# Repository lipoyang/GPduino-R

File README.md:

GPduino-R
=========

## 概要
GPduino-Rは、ESP8266搭載のWiFiロボット制御ボードです。

以下のことができます。
* ラジコンサーボ最大16個を制御
* DCモータ2個を制御 (最大連続1.2A / 最大瞬間3.0A)
* 電源 3.6V～7.2V (4.8～6V推奨)、電源電圧を監視
* WiFiによる通信　(APにもSTAにもなれる)

## ファイル一覧

* hard/GPduino-R/
	* GPduino-R.sch/brd: 回路/基板設計データ(Eagle形式)
	* GPduino-R.pdf: 回路図(PDF)
	* GPduino-R_BOM.xlsx: BOMリスト(Excel形式)
	* GPduino-R.GBL/GBO/GBP/GBS/GML/GTL/GTO/GTP/GTS/TXT: ガーバデータ
* firm/
	* GPduinoR/: Arduinoライブライリ
	* Mini4LD/Mini4LD.ino: 四足歩行ロボットのArduinoスケッチ
* LICENSE: Apache Licence 2.0です。
	* ただし、回路/基板設計は、Creative Commons Attribution Share-Alike 3.0です。
* README.md これ

## Arduino開発環境のセットアップ
GPduino-R はESP8266を搭載しており、Arduinoでファームウェアを開発できます。

* まず、ArduinoIDE をインストールしておきます。 (ここでは 1.6.9 を使用)
* [ファイル] > [環境設定] > [Additional Boards Manager URLs:]に下記URLをコピペ
	* http://arduino.esp8266.com/stable/package_esp8266com_index.json (安定版)
	* http://arduino.esp8266.com/staging/package_esp8266com_index.json (開発版)
* [ツール] > [ボード] > [ボードマネージャ] で [esp8266] をインストール
* [ツール] > [ボード] で [Generic ESP8266 Module]を選択
	* Flash Mode : QIO
	* Flash Frequency : 40MHz
	* Upload Using : Serial
	* CPU Frequency : 80MHz
	* Flash Size : 4M(3M SPIFFS)　(3MBをファイルシステムで使用 / 1MBをスケッチで使用)
	* Debug port : Disabled
	* Debug Level : None
	* Reset Method : nodemcu
	* Upload Speed : 115200

## Arduinoライブラリのインストール

firm/ にある GPduinoR/ フォルダを、Arduinoのライブラリフォルダにコピーします。

Arduinoのライブラリフォルダは、以下の場所です。
* Documents/Arduino/libraries (Windows10, Mac, Linux)
* My Documents/Arduino/libraries (Windows7)

## Arduinoスケッチの作成
GPduinoR.h をインクルードします。
``` c
#include <GPduinoR.h>
```
すると、以下のオブジェクトが使用できます。詳細は、GPduinoR/フォルダにあるソースを参照してください。
- Battery: バッテリー電圧の取得
- DcMotor: DCモータの制御
- RcServo: ラジコンサーボの制御
- UdpComm: WiFiによるUDP/IP通信

Mini4LD/Mini4LD.ino は、四足歩行ロボット([歩くミニ四駆](https://www.youtube.com/watch?v=Bx3RYRKqrKQ))のArduinoスケッチです。参考にしてください。

## Arduinoスケッチの書き込み

* GPduino-RをUSBケーブルでPCに接続します。
* 書き込み時もUSBからの給電は受けません。CN1から給電してください。
* Windows 7以降であればドライバが自動でインストールされ、COMポートとして認識されます。
	* 自動でデバイスが認識されない環境ではFTDIのデバイスドライバをインストールしてください。
* [ツール] > [シリアルポート]でGPduino-RのCOMポート番号を指定します。
* BOOTボタン(SW2)を押し下げた状態で、RESETボタン(SW1)を押して離します。
* Uploadボタンで、ファームウェアを書き込みます。

## 既知の問題点
* サーボのコネクタの間隔が狭すぎる。(干渉して16個全部を接続できない)

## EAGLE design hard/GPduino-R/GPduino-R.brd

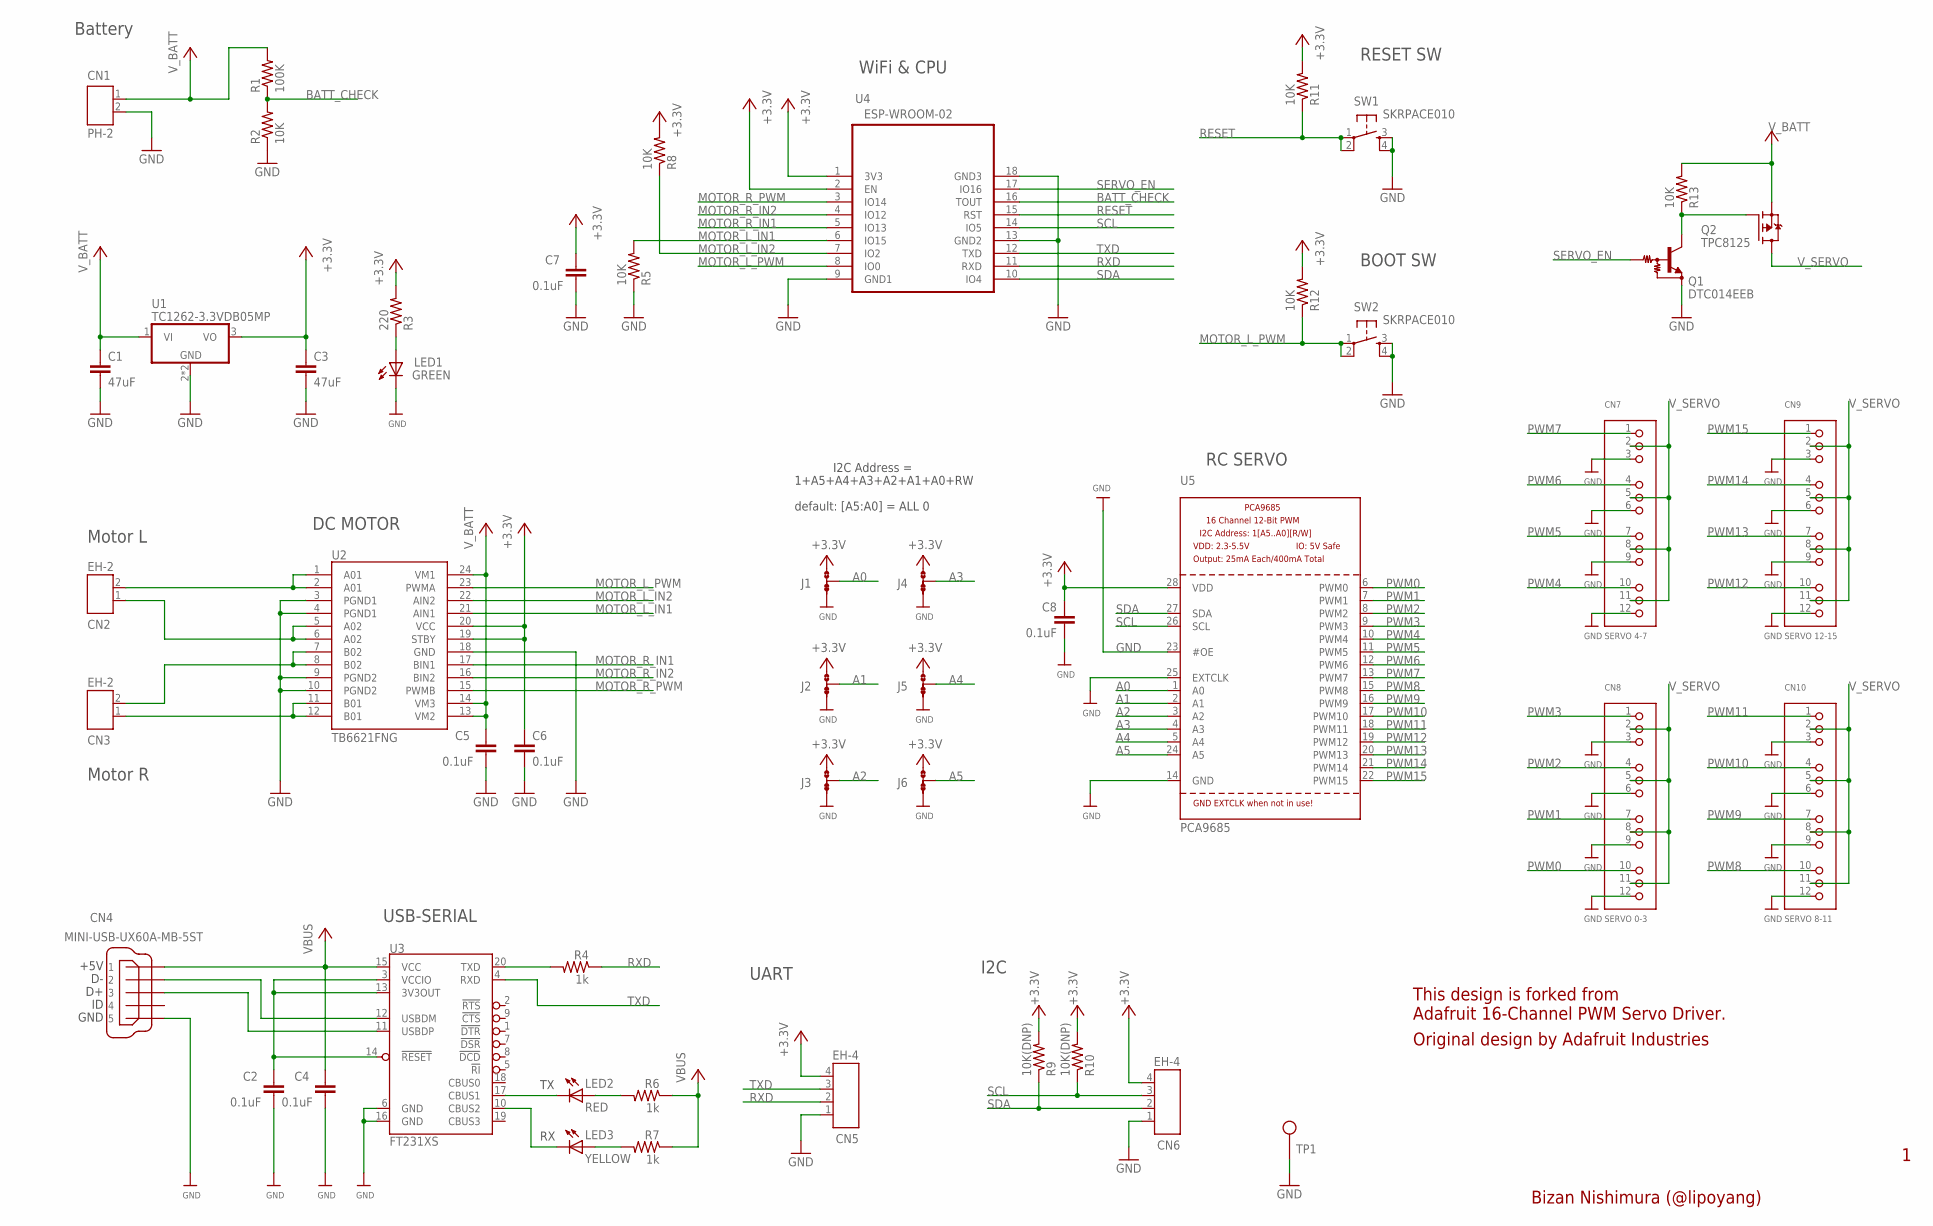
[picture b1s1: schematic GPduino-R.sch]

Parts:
C1, C3: 47uF; C3216
C2, C4, C5, C6, C7, C8: 0.1uF; C1608
CN1: PH-2
CN2, CN3: EH-2
CN4: MINI-USB-UX60A-MB-5ST; UX60A-MB-5ST
CN5, CN6: EH-4
CN7: SERVO 4-7; 3X04
CN8: SERVO 0-3; 3X04
CN9: SERVO 12-15; 3X04
CN10: SERVO 8-11; 3X04
J1, J2, J3, J4, J5, J6: JUMP-SHORTB; JUMP-SHORT
LED1: GREEN; CHIPLED_0603
LED2: RED; CHIPLED_0603
LED3: YELLOW; CHIPLED_0603
Q1: DTC014EEB; SOT490
Q2: TPC8125; SO-8
R1: 100K; 0603-RES
R2, R5, R8, R11, R12, R13: 10K; 0603-RES
R3: 220; 0603-RES
R4, R6, R7: 1k; 0603-RES
R9, R10: 10K(DNP); 0603-RES
SW1, SW2: SKRPACE010
TP1: TEST_PIN
U1: TC1262-3.3VDB05MP; SOT223
U2: TB6621FNG; SSOP24
U3: FT231XS; SSOP20
U4: ESP-WROOM-02; FRONT-FACE
U5: PCA9685; TSSOP28

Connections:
+3V3: C3.1, C6.1, C7.1, C8.1, CN5.4, CN6.4, J1.1, J2.1, J3.1, J4.1, J5.1, J6.1, R3.2, R8.2, R9.2, R10.2, R11.2, R12.2, U1.3 (VO), U2.19 (STBY), U2.20 (VCC), U4.1 (3V3), U4.2 (EN), U5.28 (VDD)
A0: J1.2, U5.1 (A0)
A01: CN2.2, U2.1 (A01), U2.2 (A01)
A1: J2.2, U5.2 (A1)
A02: CN2.1, U2.5 (A02), U2.6 (A02)
A2: J3.2, U5.3 (A2)
A3: J4.2, U5.4 (A3)
A4: J5.2, U5.5 (A4)
A5: J6.2, U5.24 (A5)
BATT_CHECK: R1.1, R2.2, U4.16 (TOUT)
GND: C1.2, C2.2, C3.2, C4.2, C5.2, C6.2, C7.2, C8.2, CN1.2, CN4.5, CN5.1, CN6.1, CN7.3, CN7.6, CN7.9, CN7.12, CN8.3, CN8.6, CN8.9, CN8.12, CN9.3, CN9.6, CN9.9, CN9.12, CN10.3, CN10.6, CN10.9, CN10.12, J1.3, J2.3, J3.3, J4.3, J5.3, J6.3, LED1.C, Q1.2 (E), R2.1, R5.1, SW1.3, SW1.4, SW2.3, SW2.4, TP1.1, U1.2 (GND), U1.4 (GND), U2.3 (PGND1), U2.4 (PGND1), U2.9 (PGND2), U2.10 (PGND2), U2.18 (GND), U3.6 (GND), U3.16 (GND), U4.9 (GND1), U4.13 (GND2), U4.18 (GND3), U5.14 (GND), U5.23 (#OE), U5.25 (EXTCLK)
MOTOR_L_IN1: R5.2, U2.21 (AIN1), U4.6 (IO15)
MOTOR_L_IN2: R8.1, U2.22 (AIN2), U4.7 (IO2)
MOTOR_L_PWM: R12.1, SW2.1, SW2.2, U2.23 (PWMA), U4.8 (IO0)
MOTOR_R_IN1: U2.17 (BIN1), U4.5 (IO13)
MOTOR_R_IN2: U2.16 (BIN2), U4.4 (IO12)
MOTOR_R_PWM: U2.15 (PWMB), U4.3 (IO14)
unnamed: LED1.A, R3.1
unnamed: R4.2, U3.20 (TXD)
unnamed: CN3.1, U2.11 (B01), U2.12 (B01)
unnamed: CN3.2, U2.7 (B02), U2.8 (B02)
unnamed: LED2.C, U3.17 (CBUS1)
unnamed: LED3.C, U3.10 (CBUS2)
unnamed: LED2.A, R6.2
unnamed: LED3.A, R7.2
unnamed: CN4.2, U3.12 (USBDM)
unnamed: CN4.3, U3.11 (USBDP)
unnamed: C2.1, U3.3 (VCCIO), U3.13 (3V3OUT), U3.14 (!RESET)
unnamed: Q1.3 (C), Q2.4 (G), R13.1
PWM0: CN8.10, U5.6 (PWM0)
PWM1: CN8.7, U5.7 (PWM1)
PWM2: CN8.4, U5.8 (PWM2)
PWM3: CN8.1, U5.9 (PWM3)
PWM4: CN7.10, U5.10 (PWM4)
PWM5: CN7.7, U5.11 (PWM5)
PWM6: CN7.4, U5.12 (PWM6)
PWM7: CN7.1, U5.13 (PWM7)
PWM8: CN10.10, U5.15 (PWM8)
PWM9: CN10.7, U5.16 (PWM9)
PWM10: CN10.4, U5.17 (PWM10)
PWM11: CN10.1, U5.18 (PWM11)
PWM12: CN9.10, U5.19 (PWM12)
PWM13: CN9.7, U5.20 (PWM13)
PWM14: CN9.4, U5.21 (PWM14)
PWM15: CN9.1, U5.22 (PWM15)
RESET: R11.1, SW1.1, SW1.2, U4.15 (RST)
RXD: CN5.2, R4.1, U4.11 (RXD)
SCL: CN6.3, R10.1, U4.14 (IO5), U5.26 (SCL)
SDA: CN6.2, R9.1, U4.10 (IO4), U5.27 (SDA)
SERVO_EN: Q1.1 (B), U4.17 (IO16)
TXD: CN5.3, U3.4 (RXD), U4.12 (TXD)
VBUS: C4.1, CN4.1, R6.1, R7.1, U3.15 (VCC)
V_BATT: C1.1, C5.1, CN1.1, Q2.1 (S), Q2.2 (S), Q2.3 (S), R1.2, R13.2, U1.1 (VI), U2.13 (VM2), U2.14 (VM3), U2.24 (VM1)
V_SERVO: CN7.2, CN7.5, CN7.8, CN7.11, CN8.2, CN8.5, CN8.8, CN8.11, CN9.2, CN9.5, CN9.8, CN9.11, CN10.2, CN10.5, CN10.8, CN10.11, Q2.5 (D), Q2.6 (D), Q2.7 (D), Q2.8 (D)

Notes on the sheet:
Battery
Motor L
Bizan Nishimura (@lipoyang)
Motor R
I2C
1+A5+A4+A3+A2+A1+A0+RW
I2C Address =
default: [A5:A0] = ALL 0
UART
USB-SERIAL
DC MOTOR
RC SERVO
WiFi & CPU
RESET SW
BOOT SW
This design is forked from Adafruit 16-Channel PWM Servo Driver.
Original design by Adafruit Industries

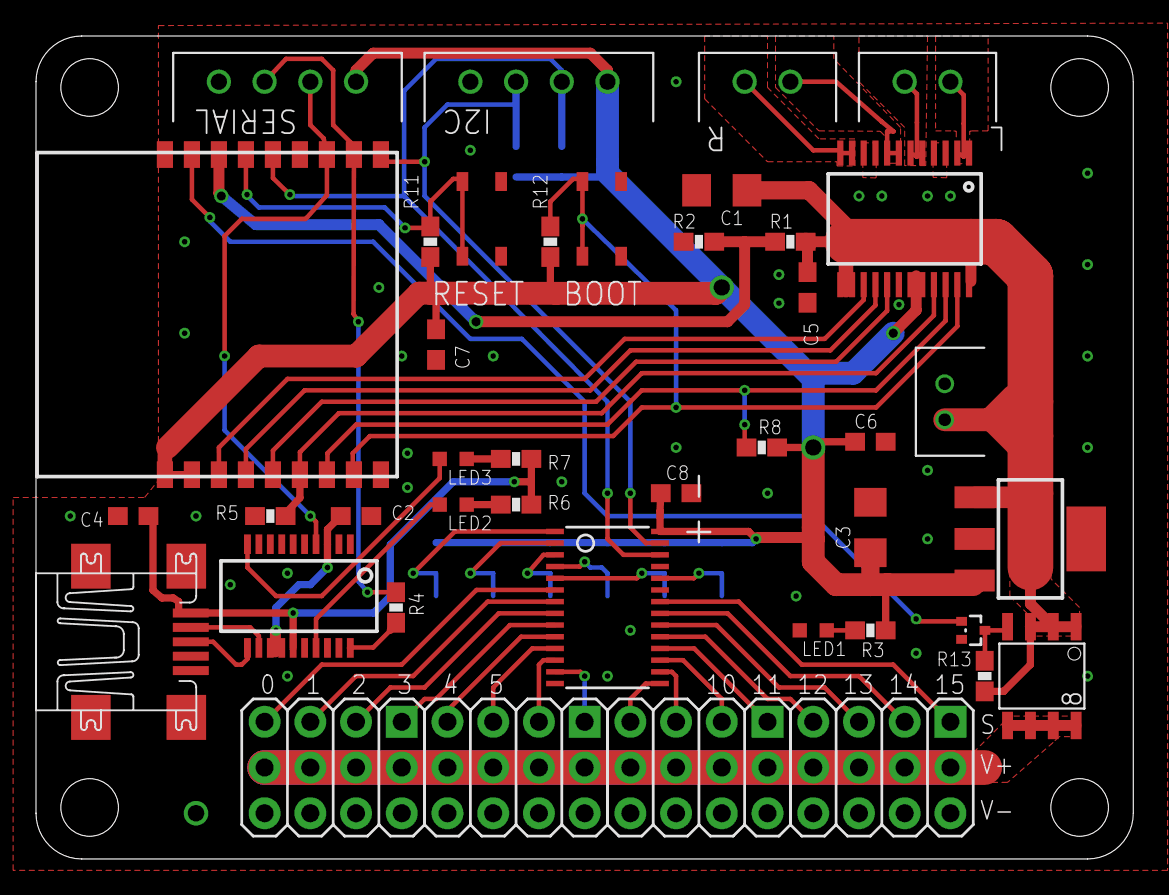
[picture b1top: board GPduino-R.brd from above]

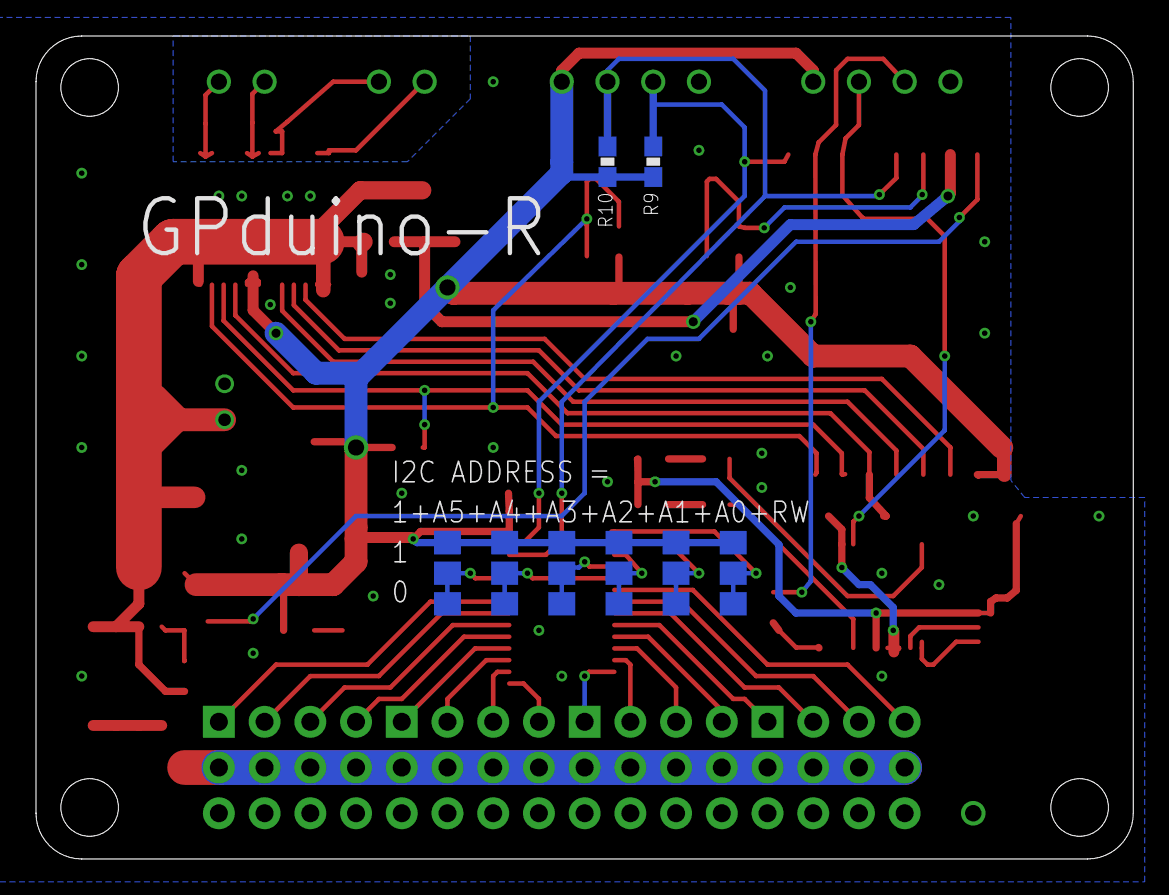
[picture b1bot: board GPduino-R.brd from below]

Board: 2 copper layers, 61.0 x 45.7 mm, 50 parts (8 on the bottom side), 54 nets.

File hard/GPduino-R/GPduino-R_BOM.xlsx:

No | Reference | Part Number | Vender | Description | DNP | Qty | Unit Price | Price | Lot Size | Supplier | Supplier Code
1 | C1,3 | 47u(3216) | (generic) | 3216型ガタ |  | 2 | 30 | 60 | 10 | 秋月アキヅキ | P-06040
2 | C2,4,5,6,7,8 | 0.1u(1608) | (generic) | 1608型ガタ |  | 6 | 0.32500000000000001 | 1.9500000000000002 | 4000 | 秋月アキヅキ | P-01299
3 | CN1 | S2B-PH-K-S | JST | PH 2極 L型ポストキョクガタ |  | 1 | 16 | 16 | 1 | 共立キョウリツ | -
4 | CN2,3 | B2B-EH-A | JST | EH 2極 I型ポストキョクガタ | DNP | 0 | 16 | 0 | 1 | 共立キョウリツ | -
5 | CN4 | MINI-USB-UX60A-MB-5ST | HRS | USB ミニB |  | 1 | 50 | 50 | 4 | 秋月アキヅキ | C-05690
6 | CN5,6 | B4B-EH-A | JST | EH 4極 I型ポストキョクガタ | DNP | 0 | 21 | 0 | 1 | 共立キョウリツ | -
7 | CN7,8,9,10 | - | (generic) | ピンヘッダ 3ピン×4 | DNP | 0 | 60 | 0 | 2 | 共立キョウリツ | -
8 | LED1 | OSYG1608 | OptoSupply | 1608型 GREENガタ |  | 1 | 10 | 10 | 20 | 秋月アキヅキ | I-03980
9 | LED2 | OSHR1608 | OptoSupply | 1608型 REDガタ |  | 1 | 10 | 10 | 20 | 秋月アキヅキ | I-03978
10 | LED3 | OSYL1608 | OptoSupply | 1608型 YELLOWガタ |  | 1 | 10 | 10 | 20 | 秋月アキヅキ | I-03984
11 | Q1 | DTC014EEB | ROHM | NPNデジタルトランジスタ |  | 1 | 3.2 | 3.2 | 200 | RS | 124-6536
12 | Q2 | TPC8125 | Toshiba | PMOS FET |  | 1 | 36.799999999999997 | 36.799999999999997 | 5 | RS | 756-3817
13 | R1 | 100k(1608) | (generic) | 1608型 |  | 1 | 0.2 | 0.2 | 2500 | 秋月アキヅキ | R-06104
14 | R2,5,8,11,12,13 | 10k(1608) | (generic) | 1608型 |  | 6 | 0.2 | 1.2000000000000002 | 2500 | 秋月アキヅキ | R-06103
15 | R3 | 220(1608) | (generic) | 1608型 |  | 1 | 0.2 | 0.2 | 2500 | 秋月アキヅキ | R-06221
16 | R4,R6,R7 | 1k(1608) | (generic) | 1608型 |  | 3 | 0.2 | 0.60000000000000009 | 2500 | 秋月アキヅキ | R-06102
17 | R9,R10 | 10k(1608) | (generic) | 1608型 | DNP | 0 | 0.2 | 0 | 2500 | 秋月アキヅキ | R-06103
18 | SW1,2 | SKRPACE010 | ALPS | 表面実装タクトスイッチヒョウメンジッソウ |  | 2 | 20 | 40 | 5 | 秋月アキヅキ | P-06185
20 | U1 | TC1262-3.3VDB05MP | Microchip | LDO, 3.3V-0.5A, SOT-223型ガタ |  | 1 | 81 | 81 | 1 | RS | 703-7905
21 | U2 | TB6621FNG | Toshiba | Dual DCモータドライバ |  | 1 | 306 | 306 | 1 | RS | 770-3797
22 | U3 | FT231XS | FTDI | USBシリアル変換ヘンカン |  | 1 | 210 | 210 | 1 | 秋月アキヅキ | I-06713
23 | U4 | ESP-WROOM-02 | Espressif Systems | ESP8266 WiFiモジュール |  | 1 | 550 | 550 | 1 | 秋月アキヅキ | M-09607
24 | U5 | PCA9685PW | NXP | PWMドライバ |  | 1 | 262 | 262 | 2 | RS | 727-5649
25 | - | - | Elecrow | 基板キバン |  | 1 | 260.10000000000002 | 260.10000000000002 | 10 | Elecrow | -
26 | - | PH2P300L | Marutsu | PH 2極 アッセンブルケーブルキョク |  | 1 | 54 | 54 | 1 | マルツ | -
 |  |  |  |  |  |  | Total | 1963.25

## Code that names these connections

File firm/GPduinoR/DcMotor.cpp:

#include <Arduino.h>

#define _DC_MOTOR_C_
#include <DcMotor.h>

// Pin Number
#define MOTOR_R_PWM    14
#define MOTOR_R_IN2    12
#define MOTOR_R_IN1    13
#define MOTOR_L_PWM    0
#define MOTOR_L_IN2    2
#define MOTOR_L_IN1    15

// begin the DC motor driver
void DcMotor_t::begin()
{
    // initialize PWM
    analogWrite(MOTOR_L_PWM, 0);
    analogWrite(MOTOR_R_PWM, 0);
    
    // initialize GPIO
    digitalWrite(MOTOR_L_IN1, LOW);
    digitalWrite(MOTOR_L_IN2, LOW);
    digitalWrite(MOTOR_R_IN1, LOW);
    digitalWrite(MOTOR_R_IN2, LOW);
    pinMode(MOTOR_L_IN1, OUTPUT);
    pinMode(MOTOR_L_IN2, OUTPUT);
    pinMode(MOTOR_R_IN1, OUTPUT);
    pinMode(MOTOR_R_IN2, OUTPUT);
}

// drive the motor
// ch: channel. MOTOR_LEFT(=0) or MOTOR_RIGHT(=1)
// value: output value (-1023 to +1023)
void DcMotor_t::out(int ch, int value)
{
    static const int IN1[]={MOTOR_L_IN1, MOTOR_R_IN1};
    static const int IN2[]={MOTOR_L_IN2, MOTOR_R_IN2};
    static const int PWM[]={MOTOR_L_PWM, MOTOR_R_PWM};
    
    int lpwm,rpwm,lin1,lin2,rin1,rin2;
    
    int pwm = abs(value);
    if(pwm<0) pwm = 0;
    if(pwm>1023) pwm = 1023;
    
    int in1,in2;
    if(value > 0){
        in1 = LOW;
        in2 = HIGH;
    }else if(value < 0){
        in1 = HIGH;
        in2 = LOW;
    }else{
        in1 = LOW;
        in2 = LOW;
        pwm = 0;
    }

    digitalWrite(IN1[ch], in1);
    digitalWrite(IN2[ch], in2);
    analogWrite(PWM[ch], pwm);
}

// drive the both motors (as a tank)
// common: common output of both motors, or translation (-1023 to +1023)
// diff: differential output of both motors, or rotation (-1023 to + 1023)
void DcMotor_t::outDiff(int common, int diff)
{
    int l,r;
    
    l = common + diff;
    r = common - diff;
    
    if(l> 1023) l= 1023;
    if(l<-1023) l=-1023;
    if(r> 1023) r= 1023;
    if(r<-1023) r=-1023;
    
    this->out(MOTOR_LEFT,  l);
    this->out(MOTOR_RIGHT, r);
}

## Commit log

2017-01-22 ファイル追加
2017-07-31 ファームウェアを追加
2017-08-01 READMEの修正

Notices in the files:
parts and their libraries:
lipoyang_frame: Released under the Creative Commons
Attribution Share-Alike 3.0 License
http://creativecommons.org/licenses/by-sa/3.0
